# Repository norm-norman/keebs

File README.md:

### Keebs

This repo contains the work for various DIY keyboards (a.k.a. Keebs).

### File Structure

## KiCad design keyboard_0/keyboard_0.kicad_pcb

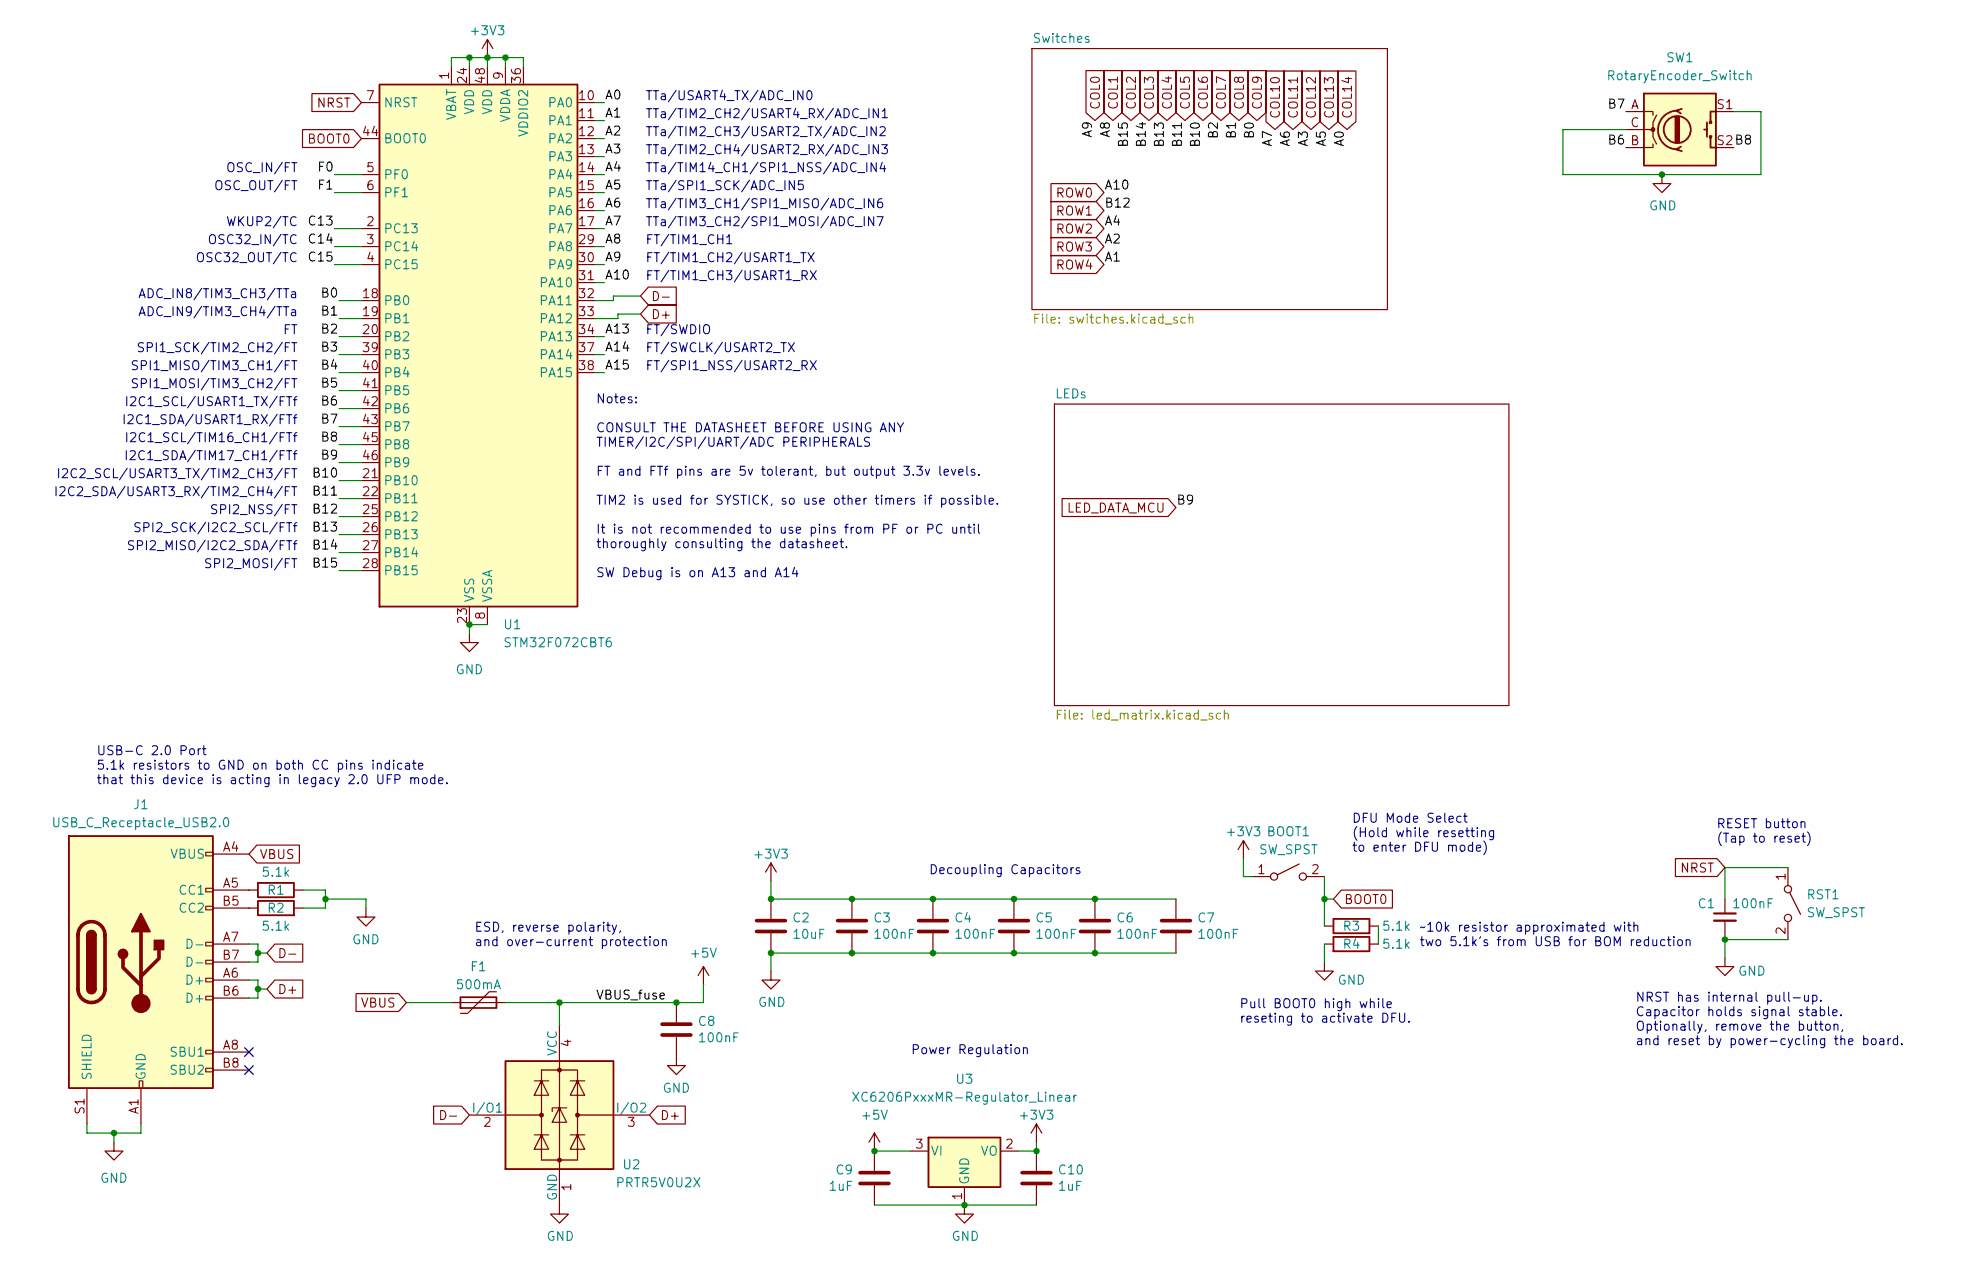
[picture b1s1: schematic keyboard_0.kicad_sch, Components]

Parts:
BOOT1: SW_SPST; SW_SPST_TL3342
C1, C3, C4, C5, C6, C7, C8: 100nF; C_0402_1005Metric; LCSC C307331
C2: 10uF; C_0603_1608Metric; LCSC C307331
C9, C10: 1uF; C_0402_1005Metric; LCSC C307331
F1: 500mA; Fuse_1206_3216Metric; LCSC C135341
J1: USB_C_Receptacle_USB2.0; USB_C_Receptacle_HRO_TYPE-C-31-M-12; JlcRotOffset 180
R1, R2, R3, R4: 5.1k; R_0402_1005Metric
RST1: SW_SPST; SW_SPST_TL3342
SW1: RotaryEncoder_Switch; ROT_Alps_EC11E-Switch
U1: STM32F072CBT6; LQFP-48_7x7mm_P0.5mm; JlcRotOffset 90
U2: PRTR5V0U2X; SOT-143; LCSC C2827688
U3: XC6206PxxxMR-Regulator_Linear; SOT-23; LCSC C5446

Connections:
+3V3: BOOT1.1 (A), C2.1, C3.1, C4.1, C5.1, C6.1, C7.1, C10.1, U1.1 (VBAT), U1.9 (VDDA), U1.24 (VDD), U1.36 (VDDIO2), U1.48 (VDD), U3.2 (VO)
+5V: C8.1, C9.1, F1.2, U2.4 (VCC), U3.3 (VI); also elsewhere on the board
/A13: U1.34 (PA13)
/A14: U1.37 (PA14)
/A15: U1.38 (PA15)
/B3: U1.39 (PB3)
/B4: U1.40 (PB4)
/B5: U1.41 (PB5)
/B6: SW1.B, U1.42 (PB6)
/B7: SW1.A, U1.43 (PB7)
/B8: SW1.S2, U1.45 (PB8)
/C13: U1.2 (PC13)
/C14: U1.3 (PC14)
/C15: U1.4 (PC15)
/F0: U1.5 (PF0)
/F1: U1.6 (PF1)
BOOT0: BOOT1.2 (B), R3.1, U1.44 (BOOT0)
COL0: U1.30 (PA9); also elsewhere on the board
COL1: U1.29 (PA8); also elsewhere on the board
COL2: U1.28 (PB15); also elsewhere on the board
COL3: U1.27 (PB14); also elsewhere on the board
COL4: U1.26 (PB13); also elsewhere on the board
COL5: U1.22 (PB11); also elsewhere on the board
COL6: U1.21 (PB10); also elsewhere on the board
COL7: U1.20 (PB2); also elsewhere on the board
COL8: U1.19 (PB1); also elsewhere on the board
COL9: U1.18 (PB0); also elsewhere on the board
COL10: U1.17 (PA7); also elsewhere on the board
COL11: U1.16 (PA6); also elsewhere on the board
COL12: U1.13 (PA3); also elsewhere on the board
COL13: U1.15 (PA5); also elsewhere on the board
COL14: U1.10 (PA0); also elsewhere on the board
D+: J1.A6 (D+), J1.B6 (D+), U1.33 (PA12), U2.3 (I/O2)
D-: J1.A7 (D-), J1.B7 (D-), U1.32 (PA11), U2.2 (I/O1)
GND: C1.2, C2.2, C3.2, C4.2, C5.2, C6.2, C7.2, C8.2, C9.2, C10.2, J1.A1 (GND), J1.A12 (GND), J1.B1 (GND), J1.B12 (GND), J1.S1 (SHIELD), R1.1, R2.2, R4.2, RST1.2 (B), SW1.C, SW1.S1, U1.8 (VSSA), U1.23 (VSS), U1.35 (VSS), U1.47 (VSS), U2.1 (GND), U3.1 (GND); also elsewhere on the board
LED_DATA_MCU: U1.46 (PB9); also elsewhere on the board
NRST: C1.1, RST1.1 (A), U1.7 (NRST)
unnamed: J1.A5 (CC1), R1.2
unnamed: J1.B5 (CC2), R2.1
unnamed: R3.2, R4.1
ROW0: U1.31 (PA10); also elsewhere on the board
ROW1: U1.25 (PB12); also elsewhere on the board
ROW2: U1.14 (PA4); also elsewhere on the board
ROW3: U1.12 (PA2); also elsewhere on the board
ROW4: U1.11 (PA1); also elsewhere on the board
VBUS: F1.1, J1.A4 (VBUS), J1.A9 (VBUS), J1.B4 (VBUS), J1.B9 (VBUS)

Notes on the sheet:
SPI1_SCK/TIM2_CH2/FT
FT/TIM1_CH1
FT/TIM1_CH3/USART1_RX
SPI2_NSS/FT
Notes: CONSULT THE DATASHEET BEFORE USING ANY TIMER/I2C/SPI/UART/ADC PERIPHERALS FT and FTf pins are 5v tolerant, but output 3.3v levels. TIM2 is used for SYSTICK, so use other timers if possible. It is not recommended to use pins from PF or PC until thoroughly consulting the datasheet. SW Debug is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
TTa/TIM2_CH4/USART2_RX/ADC_IN3
NRST has internal pull-up. Capacitor holds signal stable. Optionally, remove the button, and reset by power-cycling the board.
FT/SWDIO
Decoupling Capacitors
SPI1_MOSI/TIM3_CH2/FT
ADC_IN9/TIM3_CH4/TTa
I2C2_SCL/USART3_TX/TIM2_CH3/FT
SPI2_MISO/I2C2_SDA/FTf
FT/SWCLK/USART2_TX
I2C1_SCL/TIM16_CH1/FTf
~10k resistor approximated with two 5.1k's from USB for BOM reduction
TTa/TIM2_CH2/USART4_RX/ADC_IN1
USB-C 2.0 Port 5.1k resistors to GND on both CC pins indicate that this device is acting in legacy 2.0 UFP mode.
TTa/TIM2_CH3/USART2_TX/ADC_IN2
OSC_IN/FT
DFU Mode Select (Hold while resetting to enter DFU mode)
WKUP2/TC
I2C2_SDA/USART3_RX/TIM2_CH4/FT
ADC_IN8/TIM3_CH3/TTa
RESET button (Tap to reset)
Pull BOOT0 high while reseting to activate DFU.
I2C1_SDA/TIM17_CH1/FTf
TTa/SPI1_SCK/ADC_IN5
TTa/TIM3_CH1/SPI1_MISO/ADC_IN6
TTa/TIM3_CH2/SPI1_MOSI/ADC_IN7
OSC32_OUT/TC
FT/SPI1_NSS/USART2_RX
SPI1_MISO/TIM3_CH1/FT
OSC32_IN/TC
TTa/TIM14_CH1/SPI1_NSS/ADC_IN4
I2C1_SDA/USART1_RX/FTf
SPI2_MOSI/FT
FT/TIM1_CH2/USART1_TX
Power Regulation
SPI2_SCK/I2C2_SCL/FTf

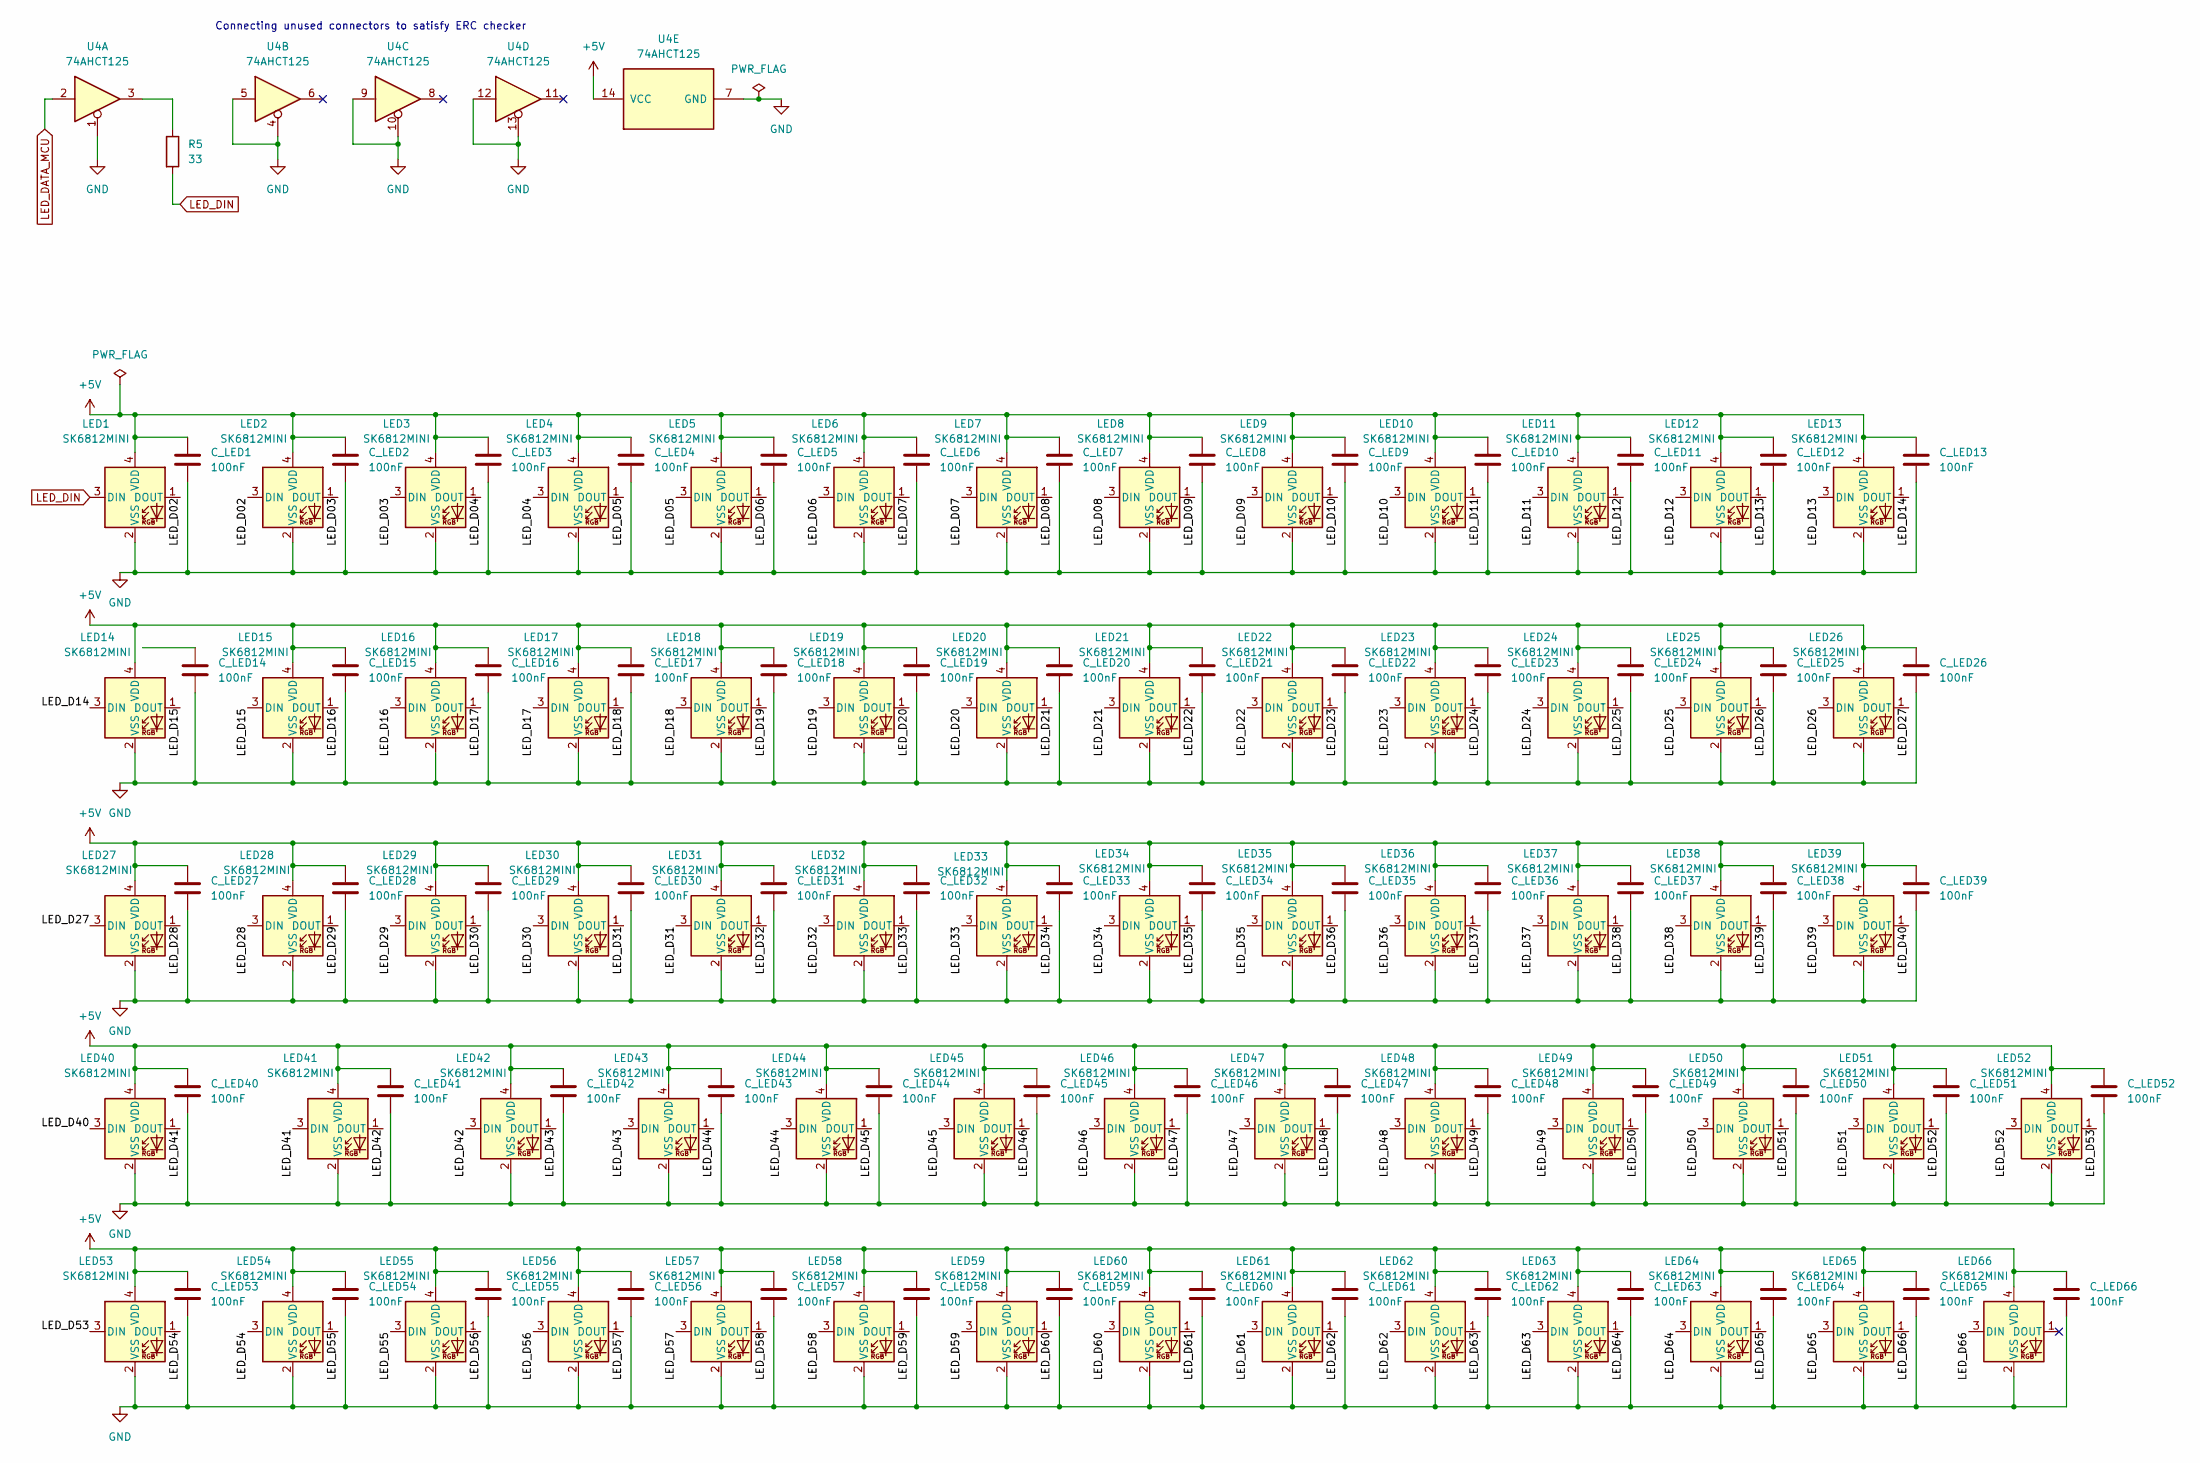
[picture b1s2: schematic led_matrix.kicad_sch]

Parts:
C_LED1, C_LED2, C_LED3, C_LED4, C_LED5, C_LED6, C_LED7, C_LED8, C_LED9, C_LED10, C_LED11, C_LED12, C_LED13, C_LED14, C_LED15, C_LED16, C_LED17, C_LED18, C_LED19, C_LED20, C_LED21, C_LED22, C_LED23, C_LED24, C_LED25, C_LED26, C_LED27, C_LED28, C_LED29, C_LED30, C_LED31, C_LED32, C_LED33, C_LED34, C_LED35, C_LED36, C_LED37, C_LED38, C_LED39, C_LED40, C_LED41, C_LED42, C_LED43, C_LED44, C_LED45, C_LED46, C_LED47, C_LED48, C_LED49, C_LED50, C_LED51, C_LED52, C_LED53, C_LED54, C_LED55, C_LED56, C_LED57, C_LED58, C_LED59, C_LED60, C_LED61, C_LED62, C_LED63, C_LED64, C_LED65, C_LED66: 100nF; C_0402_1005Metric
LED1, LED2, LED3, LED4, LED5, LED6, LED7, LED8, LED9, LED10, LED11, LED12, LED13, LED14, LED15, LED16, LED17, LED18, LED19, LED20, LED21, LED22, LED23, LED24, LED25, LED26, LED27, LED28, LED29, LED30, LED31, LED32, LED33, LED34, LED35, LED36, LED37, LED38, LED39, LED40, LED41, LED42, LED43, LED44, LED45, LED46, LED47, LED48, LED49, LED50, LED51, LED52, LED53, LED54, LED55, LED56, LED57, LED58, LED59, LED60, LED61, LED62, LED63, LED64, LED65, LED66: SK6812MINI; LED_SK6812MINI_PLCC4_3.5x3.5mm_P1.75mm
R5: 33; R_0402_1005Metric
U4: 74AHCT125; SOIC-14W_7.5x9mm_P1.27mm

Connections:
+5V: C_LED1.1, C_LED2.1, C_LED3.1, C_LED4.1, C_LED5.1, C_LED6.1, C_LED7.1, C_LED8.1, C_LED9.1, C_LED10.1, C_LED11.1, C_LED12.1, C_LED13.1, C_LED15.1, C_LED16.1, C_LED17.1, C_LED18.1, C_LED19.1, C_LED20.1, C_LED21.1, C_LED22.1, C_LED23.1, C_LED24.1, C_LED25.1, C_LED26.1, C_LED27.1, C_LED28.1, C_LED29.1, C_LED30.1, C_LED31.1, C_LED32.1, C_LED33.1, C_LED34.1, C_LED35.1, C_LED36.1, C_LED37.1, C_LED38.1, C_LED39.1, C_LED40.1, C_LED41.1, C_LED42.1, C_LED43.1, C_LED44.1, C_LED45.1, C_LED46.1, C_LED47.1, C_LED48.1, C_LED49.1, C_LED50.1, C_LED51.1, C_LED52.1, C_LED53.1, C_LED54.1, C_LED55.1, C_LED56.1, C_LED57.1, C_LED58.1, C_LED59.1, C_LED60.1, C_LED61.1, C_LED62.1, C_LED63.1, C_LED64.1, C_LED65.1, C_LED66.1, LED1.4 (VDD), LED2.4 (VDD), LED3.4 (VDD), LED4.4 (VDD), LED5.4 (VDD), LED6.4 (VDD), LED7.4 (VDD), LED8.4 (VDD), LED9.4 (VDD), LED10.4 (VDD), LED11.4 (VDD), LED12.4 (VDD), LED13.4 (VDD), LED14.4 (VDD), LED15.4 (VDD), LED16.4 (VDD), LED17.4 (VDD), LED18.4 (VDD), LED19.4 (VDD), LED20.4 (VDD), LED21.4 (VDD), LED22.4 (VDD), LED23.4 (VDD), LED24.4 (VDD), LED25.4 (VDD), LED26.4 (VDD), LED27.4 (VDD), LED28.4 (VDD), LED29.4 (VDD), LED30.4 (VDD), LED31.4 (VDD), LED32.4 (VDD), LED33.4 (VDD), LED34.4 (VDD), LED35.4 (VDD), LED36.4 (VDD), LED37.4 (VDD), LED38.4 (VDD), LED39.4 (VDD), LED40.4 (VDD), LED41.4 (VDD), LED42.4 (VDD), LED43.4 (VDD), LED44.4 (VDD), LED45.4 (VDD), LED46.4 (VDD), LED47.4 (VDD), LED48.4 (VDD), LED49.4 (VDD), LED50.4 (VDD), LED51.4 (VDD), LED52.4 (VDD), LED53.4 (VDD), LED54.4 (VDD), LED55.4 (VDD), LED56.4 (VDD), LED57.4 (VDD), LED58.4 (VDD), LED59.4 (VDD), LED60.4 (VDD), LED61.4 (VDD), LED62.4 (VDD), LED63.4 (VDD), LED64.4 (VDD), LED65.4 (VDD), LED66.4 (VDD), U4.14 (VCC); also elsewhere on the board
/LEDs/LED_D02: LED1.1 (DOUT), LED2.3 (DIN)
/LEDs/LED_D03: LED2.1 (DOUT), LED3.3 (DIN)
/LEDs/LED_D04: LED3.1 (DOUT), LED4.3 (DIN)
/LEDs/LED_D05: LED4.1 (DOUT), LED5.3 (DIN)
/LEDs/LED_D06: LED5.1 (DOUT), LED6.3 (DIN)
/LEDs/LED_D07: LED6.1 (DOUT), LED7.3 (DIN)
/LEDs/LED_D08: LED7.1 (DOUT), LED8.3 (DIN)
/LEDs/LED_D09: LED8.1 (DOUT), LED9.3 (DIN)
/LEDs/LED_D10: LED9.1 (DOUT), LED10.3 (DIN)
/LEDs/LED_D11: LED10.1 (DOUT), LED11.3 (DIN)
/LEDs/LED_D12: LED11.1 (DOUT), LED12.3 (DIN)
/LEDs/LED_D13: LED12.1 (DOUT), LED13.3 (DIN)
/LEDs/LED_D14: LED13.1 (DOUT), LED14.3 (DIN)
/LEDs/LED_D15: LED14.1 (DOUT), LED15.3 (DIN)
/LEDs/LED_D16: LED15.1 (DOUT), LED16.3 (DIN)
/LEDs/LED_D17: LED16.1 (DOUT), LED17.3 (DIN)
/LEDs/LED_D18: LED17.1 (DOUT), LED18.3 (DIN)
/LEDs/LED_D19: LED18.1 (DOUT), LED19.3 (DIN)
/LEDs/LED_D20: LED19.1 (DOUT), LED20.3 (DIN)
/LEDs/LED_D21: LED20.1 (DOUT), LED21.3 (DIN)
/LEDs/LED_D22: LED21.1 (DOUT), LED22.3 (DIN)
/LEDs/LED_D23: LED22.1 (DOUT), LED23.3 (DIN)
/LEDs/LED_D24: LED23.1 (DOUT), LED24.3 (DIN)
/LEDs/LED_D25: LED24.1 (DOUT), LED25.3 (DIN)
/LEDs/LED_D26: LED25.1 (DOUT), LED26.3 (DIN)
/LEDs/LED_D27: LED26.1 (DOUT), LED27.3 (DIN)
/LEDs/LED_D28: LED27.1 (DOUT), LED28.3 (DIN)
/LEDs/LED_D29: LED28.1 (DOUT), LED29.3 (DIN)
/LEDs/LED_D30: LED29.1 (DOUT), LED30.3 (DIN)
/LEDs/LED_D31: LED30.1 (DOUT), LED31.3 (DIN)
/LEDs/LED_D32: LED31.1 (DOUT), LED32.3 (DIN)
/LEDs/LED_D33: LED32.1 (DOUT), LED33.3 (DIN)
/LEDs/LED_D34: LED33.1 (DOUT), LED34.3 (DIN)
/LEDs/LED_D35: LED34.1 (DOUT), LED35.3 (DIN)
/LEDs/LED_D36: LED35.1 (DOUT), LED36.3 (DIN)
/LEDs/LED_D37: LED36.1 (DOUT), LED37.3 (DIN)
/LEDs/LED_D38: LED37.1 (DOUT), LED38.3 (DIN)
/LEDs/LED_D39: LED38.1 (DOUT), LED39.3 (DIN)
/LEDs/LED_D40: LED39.1 (DOUT), LED40.3 (DIN)
/LEDs/LED_D41: LED40.1 (DOUT), LED41.3 (DIN)
/LEDs/LED_D42: LED41.1 (DOUT), LED42.3 (DIN)
/LEDs/LED_D43: LED42.1 (DOUT), LED43.3 (DIN)
/LEDs/LED_D44: LED43.1 (DOUT), LED44.3 (DIN)
/LEDs/LED_D45: LED44.1 (DOUT), LED45.3 (DIN)
/LEDs/LED_D46: LED45.1 (DOUT), LED46.3 (DIN)
/LEDs/LED_D47: LED46.1 (DOUT), LED47.3 (DIN)
/LEDs/LED_D48: LED47.1 (DOUT), LED48.3 (DIN)
/LEDs/LED_D49: LED48.1 (DOUT), LED49.3 (DIN)
/LEDs/LED_D50: LED49.1 (DOUT), LED50.3 (DIN)
/LEDs/LED_D51: LED50.1 (DOUT), LED51.3 (DIN)
/LEDs/LED_D52: LED51.1 (DOUT), LED52.3 (DIN)
/LEDs/LED_D53: LED52.1 (DOUT), LED53.3 (DIN)
/LEDs/LED_D54: LED53.1 (DOUT), LED54.3 (DIN)
/LEDs/LED_D55: LED54.1 (DOUT), LED55.3 (DIN)
/LEDs/LED_D56: LED55.1 (DOUT), LED56.3 (DIN)
/LEDs/LED_D57: LED56.1 (DOUT), LED57.3 (DIN)
/LEDs/LED_D58: LED57.1 (DOUT), LED58.3 (DIN)
/LEDs/LED_D59: LED58.1 (DOUT), LED59.3 (DIN)
/LEDs/LED_D60: LED59.1 (DOUT), LED60.3 (DIN)
/LEDs/LED_D61: LED60.1 (DOUT), LED61.3 (DIN)
/LEDs/LED_D62: LED61.1 (DOUT), LED62.3 (DIN)
/LEDs/LED_D63: LED62.1 (DOUT), LED63.3 (DIN)
/LEDs/LED_D64: LED63.1 (DOUT), LED64.3 (DIN)
/LEDs/LED_D65: LED64.1 (DOUT), LED65.3 (DIN)
/LEDs/LED_D66: LED65.1 (DOUT), LED66.3 (DIN)
GND: C_LED1.2, C_LED2.2, C_LED3.2, C_LED4.2, C_LED5.2, C_LED6.2, C_LED7.2, C_LED8.2, C_LED9.2, C_LED10.2, C_LED11.2, C_LED12.2, C_LED13.2, C_LED14.2, C_LED15.2, C_LED16.2, C_LED17.2, C_LED18.2, C_LED19.2, C_LED20.2, C_LED21.2, C_LED22.2, C_LED23.2, C_LED24.2, C_LED25.2, C_LED26.2, C_LED27.2, C_LED28.2, C_LED29.2, C_LED30.2, C_LED31.2, C_LED32.2, C_LED33.2, C_LED34.2, C_LED35.2, C_LED36.2, C_LED37.2, C_LED38.2, C_LED39.2, C_LED40.2, C_LED41.2, C_LED42.2, C_LED43.2, C_LED44.2, C_LED45.2, C_LED46.2, C_LED47.2, C_LED48.2, C_LED49.2, C_LED50.2, C_LED51.2, C_LED52.2, C_LED53.2, C_LED54.2, C_LED55.2, C_LED56.2, C_LED57.2, C_LED58.2, C_LED59.2, C_LED60.2, C_LED61.2, C_LED62.2, C_LED63.2, C_LED64.2, C_LED65.2, C_LED66.2, LED1.2 (VSS), LED2.2 (VSS), LED3.2 (VSS), LED4.2 (VSS), LED5.2 (VSS), LED6.2 (VSS), LED7.2 (VSS), LED8.2 (VSS), LED9.2 (VSS), LED10.2 (VSS), LED11.2 (VSS), LED12.2 (VSS), LED13.2 (VSS), LED14.2 (VSS), LED15.2 (VSS), LED16.2 (VSS), LED17.2 (VSS), LED18.2 (VSS), LED19.2 (VSS), LED20.2 (VSS), LED21.2 (VSS), LED22.2 (VSS), LED23.2 (VSS), LED24.2 (VSS), LED25.2 (VSS), LED26.2 (VSS), LED27.2 (VSS), LED28.2 (VSS), LED29.2 (VSS), LED30.2 (VSS), LED31.2 (VSS), LED32.2 (VSS), LED33.2 (VSS), LED34.2 (VSS), LED35.2 (VSS), LED36.2 (VSS), LED37.2 (VSS), LED38.2 (VSS), LED39.2 (VSS), LED40.2 (VSS), LED41.2 (VSS), LED42.2 (VSS), LED43.2 (VSS), LED44.2 (VSS), LED45.2 (VSS), LED46.2 (VSS), LED47.2 (VSS), LED48.2 (VSS), LED49.2 (VSS), LED50.2 (VSS), LED51.2 (VSS), LED52.2 (VSS), LED53.2 (VSS), LED54.2 (VSS), LED55.2 (VSS), LED56.2 (VSS), LED57.2 (VSS), LED58.2 (VSS), LED59.2 (VSS), LED60.2 (VSS), LED61.2 (VSS), LED62.2 (VSS), LED63.2 (VSS), LED64.2 (VSS), LED65.2 (VSS), LED66.2 (VSS), U4.1, U4.4, U4.5, U4.7 (GND), U4.9, U4.10, U4.12, U4.13; also elsewhere on the board
LED_DATA_MCU: U4.2; also elsewhere on the board
LED_DIN: LED1.3 (DIN), R5.2
unnamed: R5.1, U4.3

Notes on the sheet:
Connecting unused connectors to satisfy ERC checker

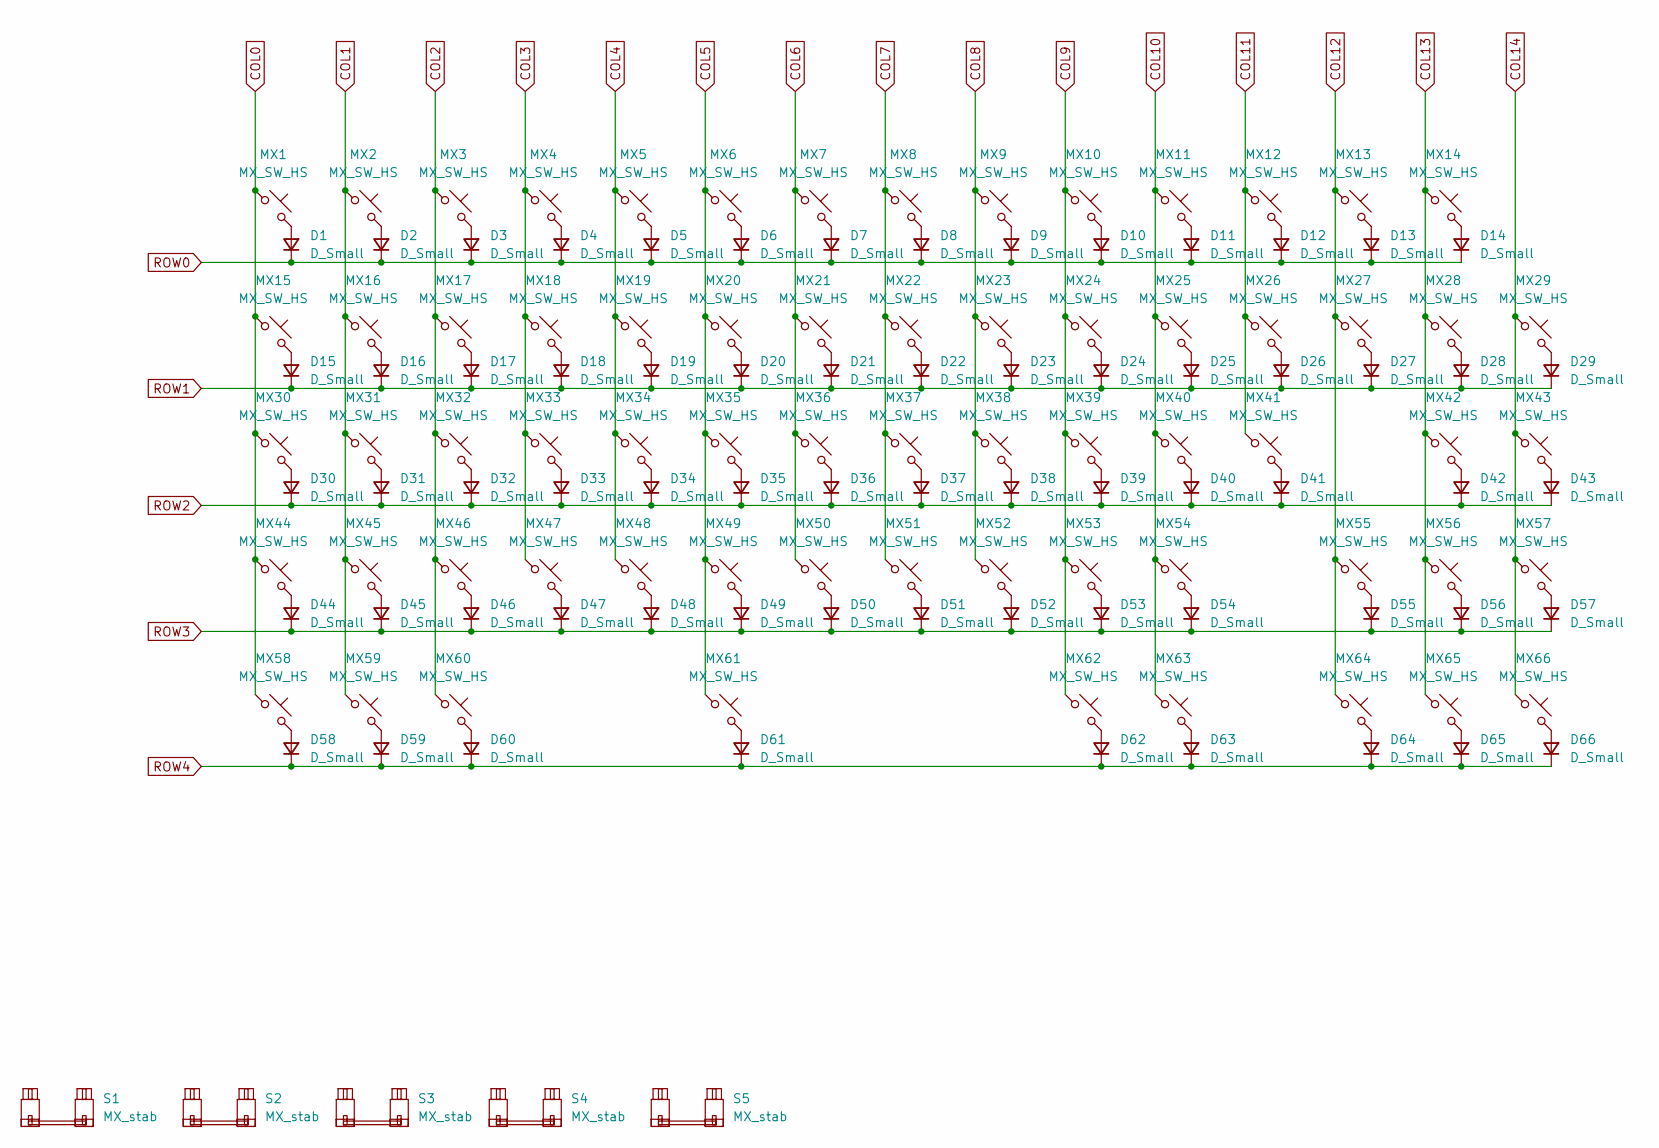
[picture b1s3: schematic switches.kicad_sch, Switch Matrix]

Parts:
D1, D2, D3, D4, D5, D6, D7, D8, D9, D10, D11, D12, D13, D14, D15, D16, D17, D18, D19, D20, D21, D22, D23, D24, D25, D26, D27, D28, D29, D30, D31, D32, D33, D34, D35, D36, D37, D38, D39, D40, D41, D42, D43, D44, D45, D46, D47, D48, D49, D50, D51, D52, D53, D54, D55, D56, D57, D58, D59, D60, D61, D62, D63, D64, D65, D66: D_Small; D_SOD-323_HandSoldering
MX1, MX2, MX3, MX4, MX5, MX6, MX7, MX8, MX9, MX10, MX11, MX12, MX13, MX16, MX17, MX18, MX19, MX20, MX21, MX22, MX23, MX24, MX25, MX26, MX27, MX29, MX31, MX32, MX33, MX34, MX35, MX36, MX37, MX38, MX39, MX40, MX41, MX43, MX45, MX46, MX47, MX48, MX49, MX50, MX51, MX52, MX53, MX54, MX56, MX57, MX64, MX65, MX66: MX_SW_HS; SW_Cherry_MX_PCB_1.00u
MX14, MX55: MX_SW_HS; SW_Cherry_MX_PCB_2.00u
MX15, MX28: MX_SW_HS; SW_Cherry_MX_PCB_1.50u
MX30: MX_SW_HS; SW_Cherry_MX_PCB_1.75u
MX42, MX44: MX_SW_HS; SW_Cherry_MX_PCB_2.25u
MX58, MX59, MX60, MX62, MX63: MX_SW_HS; SW_Cherry_MX_PCB_1.25u
MX61: MX_SW_HS; SW_Cherry_MX_PCB_6.25u
S1, S4: MX_stab; STAB_MX_P_2.25u
S2: MX_stab; STAB_MX_P_6.25u
S3, S5: MX_stab; STAB_MX_P_2u

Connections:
COL0: MX1.1, MX15.1, MX30.1, MX44.1, MX58.1; also elsewhere on the board
COL1: MX2.1, MX16.1, MX31.1, MX45.1, MX59.1; also elsewhere on the board
COL2: MX3.1, MX17.1, MX32.1, MX46.1, MX60.1; also elsewhere on the board
COL3: MX4.1, MX18.1, MX33.1, MX47.1; also elsewhere on the board
COL4: MX5.1, MX19.1, MX34.1, MX48.1; also elsewhere on the board
COL5: MX6.1, MX20.1, MX35.1, MX49.1, MX61.1; also elsewhere on the board
COL6: MX7.1, MX21.1, MX36.1, MX50.1; also elsewhere on the board
COL7: MX8.1, MX22.1, MX37.1, MX51.1; also elsewhere on the board
COL8: MX9.1, MX23.1, MX38.1, MX52.1; also elsewhere on the board
COL9: MX10.1, MX24.1, MX39.1, MX53.1, MX62.1; also elsewhere on the board
COL10: MX11.1, MX25.1, MX40.1, MX54.1, MX63.1; also elsewhere on the board
COL11: MX12.1, MX26.1, MX41.1; also elsewhere on the board
COL12: MX13.1, MX27.1, MX55.1, MX64.1; also elsewhere on the board
COL13: MX14.1, MX28.1, MX42.1, MX56.1, MX65.1; also elsewhere on the board
COL14: MX29.1, MX43.1, MX57.1, MX66.1; also elsewhere on the board
unnamed: D1.2 (A), MX1.2
unnamed: D2.2 (A), MX2.2
unnamed: D3.2 (A), MX3.2
unnamed: D4.2 (A), MX4.2
unnamed: D5.2 (A), MX5.2
unnamed: D6.2 (A), MX6.2
unnamed: D7.2 (A), MX7.2
unnamed: D8.2 (A), MX8.2
unnamed: D9.2 (A), MX9.2
unnamed: D10.2 (A), MX10.2
unnamed: D11.2 (A), MX11.2
unnamed: D12.2 (A), MX12.2
unnamed: D13.2 (A), MX13.2
unnamed: D14.2 (A), MX14.2
unnamed: D15.2 (A), MX15.2
unnamed: D16.2 (A), MX16.2
unnamed: D17.2 (A), MX17.2
unnamed: D18.2 (A), MX18.2
unnamed: D19.2 (A), MX19.2
unnamed: D20.2 (A), MX20.2
unnamed: D21.2 (A), MX21.2
unnamed: D22.2 (A), MX22.2
unnamed: D23.2 (A), MX23.2
unnamed: D24.2 (A), MX24.2
unnamed: D25.2 (A), MX25.2
unnamed: D26.2 (A), MX26.2
unnamed: D27.2 (A), MX27.2
unnamed: D28.2 (A), MX28.2
unnamed: D29.2 (A), MX29.2
unnamed: D30.2 (A), MX30.2
unnamed: D31.2 (A), MX31.2
unnamed: D32.2 (A), MX32.2
unnamed: D33.2 (A), MX33.2
unnamed: D34.2 (A), MX34.2
unnamed: D35.2 (A), MX35.2
unnamed: D36.2 (A), MX36.2
unnamed: D37.2 (A), MX37.2
unnamed: D38.2 (A), MX38.2
unnamed: D39.2 (A), MX39.2
unnamed: D40.2 (A), MX40.2
unnamed: D41.2 (A), MX41.2
unnamed: D42.2 (A), MX42.2
unnamed: D43.2 (A), MX43.2
unnamed: D44.2 (A), MX44.2
unnamed: D45.2 (A), MX45.2
unnamed: D46.2 (A), MX46.2
unnamed: D47.2 (A), MX47.2
unnamed: D48.2 (A), MX48.2
unnamed: D49.2 (A), MX49.2
unnamed: D50.2 (A), MX50.2
unnamed: D51.2 (A), MX51.2
unnamed: D52.2 (A), MX52.2
unnamed: D53.2 (A), MX53.2
unnamed: D54.2 (A), MX54.2
unnamed: D55.2 (A), MX55.2
unnamed: D56.2 (A), MX56.2
unnamed: D57.2 (A), MX57.2
unnamed: D58.2 (A), MX58.2
unnamed: D59.2 (A), MX59.2
unnamed: D60.2 (A), MX60.2
unnamed: D61.2 (A), MX61.2
unnamed: D62.2 (A), MX62.2
unnamed: D63.2 (A), MX63.2
unnamed: D64.2 (A), MX64.2
unnamed: D65.2 (A), MX65.2
unnamed: D66.2 (A), MX66.2
ROW0: D1.1 (K), D2.1 (K), D3.1 (K), D4.1 (K), D5.1 (K), D6.1 (K), D7.1 (K), D8.1 (K), D9.1 (K), D10.1 (K), D11.1 (K), D12.1 (K), D13.1 (K), D14.1 (K); also elsewhere on the board
ROW1: D15.1 (K), D16.1 (K), D17.1 (K), D18.1 (K), D19.1 (K), D20.1 (K), D21.1 (K), D22.1 (K), D23.1 (K), D24.1 (K), D25.1 (K), D26.1 (K), D27.1 (K), D28.1 (K), D29.1 (K); also elsewhere on the board
ROW2: D30.1 (K), D31.1 (K), D32.1 (K), D33.1 (K), D34.1 (K), D35.1 (K), D36.1 (K), D37.1 (K), D38.1 (K), D39.1 (K), D40.1 (K), D41.1 (K), D42.1 (K), D43.1 (K); also elsewhere on the board
ROW3: D44.1 (K), D45.1 (K), D46.1 (K), D47.1 (K), D48.1 (K), D49.1 (K), D50.1 (K), D51.1 (K), D52.1 (K), D53.1 (K), D54.1 (K), D55.1 (K), D56.1 (K), D57.1 (K); also elsewhere on the board
ROW4: D58.1 (K), D59.1 (K), D60.1 (K), D61.1 (K), D62.1 (K), D63.1 (K), D64.1 (K), D65.1 (K), D66.1 (K); also elsewhere on the board

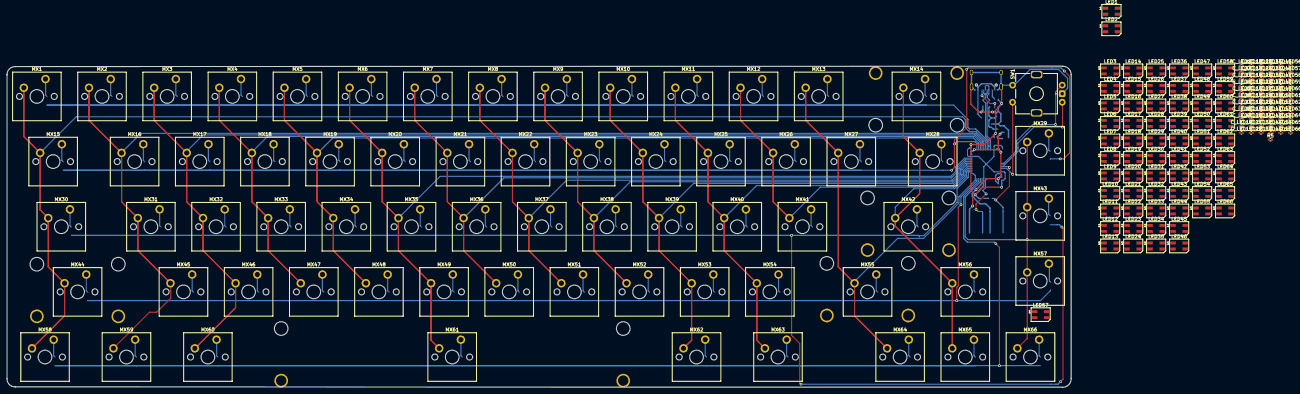
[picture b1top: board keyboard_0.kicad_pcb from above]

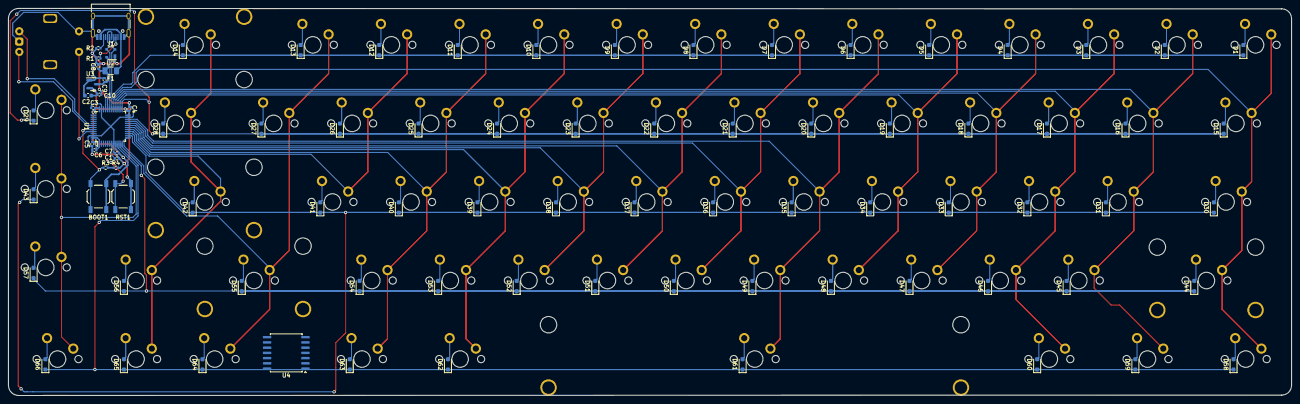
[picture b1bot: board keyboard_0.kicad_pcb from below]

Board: 2 copper layers, 311.1 x 93.9 mm, 292 parts (88 on the bottom side), 166 nets.

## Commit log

2025-10-08 add gitignore
2026-02-27 pcb with switches routed and nothing special yet
2026-02-27 update changes
2026-02-28 update to use prebuilt mcu pcb
2026-03-01 latest changes - incomplete routing
2026-03-10 connect rest of switches and bring in aux components
2026-03-10 include pcb changes
2026-03-10 bring back switches and separate sub sheets
2026-03-21 add led matrix schematic and finish adding rotary knob
